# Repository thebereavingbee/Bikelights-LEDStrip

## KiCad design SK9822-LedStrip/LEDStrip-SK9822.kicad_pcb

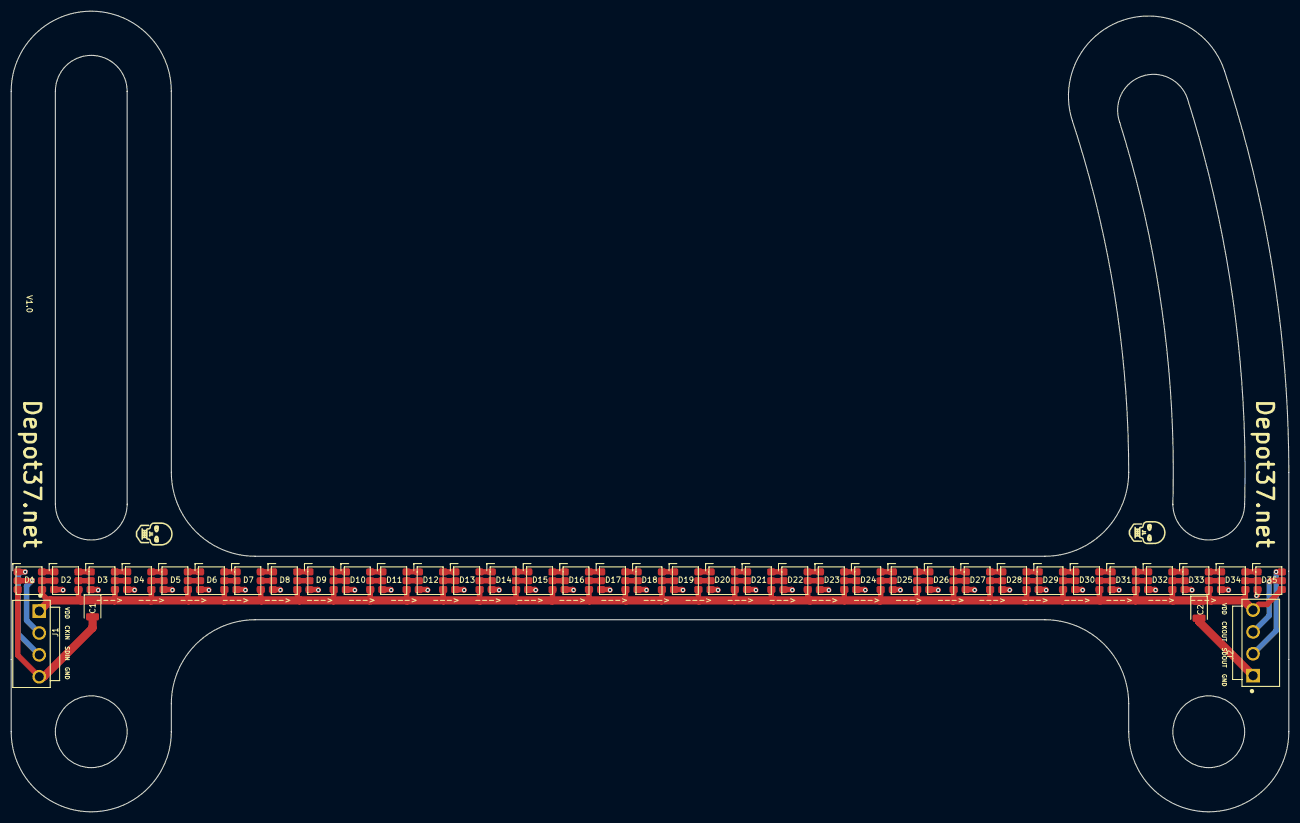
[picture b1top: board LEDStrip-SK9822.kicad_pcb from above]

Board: 2 copper layers, 231.4 x 145.0 mm, 39 parts (0 on the bottom side), 74 nets.

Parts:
C1, C2: 100uF; CP_EIA-3528-15_AVX-H
D1, D2, D3, D4, D5, D6, D7, D8, D9, D10, D11, D12, D13, D14, D15, D16, D17, D18, D19, D20, D21, D22, D23, D24, D25, D26, D27, D28, D29, D30, D31, D32, D33, D34, D35: SK9822
J1, J2: TE_1-1123723-4

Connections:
/CKIN: D1.2, J1.2
/CKOUT: D35.5, J2.3
/GND: C1.2, C2.2, D1.3, D2.3, D3.3, D4.3, D5.3, D6.3, D7.3, D8.3, D9.3, D10.3, D11.3, D12.3, D13.3, D14.3, D15.3, D16.3, D17.3, D18.3, D19.3, D20.3, D21.3, D22.3, D23.3, D24.3, D25.3, D26.3, D27.3, D28.3, D29.3, D30.3, D31.3, D32.3, D33.3, D34.3, D35.3, J1.4, J2.1
/SDIN: D1.1, J1.3
/SDOUT: D35.6, J2.2
/VDD: C1.1, C2.1, D1.4, D2.4, D3.4, D4.4, D5.4, D6.4, D7.4, D8.4, D9.4, D10.4, D11.4, D12.4, D13.4, D14.4, D15.4, D16.4, D17.4, D18.4, D19.4, D20.4, D21.4, D22.4, D23.4, D24.4, D25.4, D26.4, D27.4, D28.4, D29.4, D30.4, D31.4, D32.4, D33.4, D34.4, D35.4, J1.1, J2.4
unnamed: D1.5, D2.2
unnamed: D1.6, D2.1
unnamed: D2.5, D3.2
unnamed: D2.6, D3.1
unnamed: D3.5, D4.2
unnamed: D3.6, D4.1
unnamed: D4.5, D5.2
unnamed: D4.6, D5.1
unnamed: D5.5, D6.2
unnamed: D5.6, D6.1
unnamed: D6.5, D7.2
unnamed: D6.6, D7.1
unnamed: D7.5, D8.2
unnamed: D7.6, D8.1
unnamed: D8.5, D9.2
unnamed: D8.6, D9.1
unnamed: D9.6, D10.1
unnamed: D9.5, D10.2
unnamed: D10.5, D11.2
unnamed: D10.6, D11.1
unnamed: D11.5, D12.2
unnamed: D11.6, D12.1
unnamed: D12.5, D13.2
unnamed: D12.6, D13.1
unnamed: D13.5, D14.2
unnamed: D13.6, D14.1
unnamed: D14.5, D15.2
unnamed: D14.6, D15.1
unnamed: D15.5, D16.2
unnamed: D15.6, D16.1
unnamed: D16.5, D17.2
unnamed: D16.6, D17.1
unnamed: D17.5, D18.2
unnamed: D17.6, D18.1
unnamed: D18.5, D19.2
unnamed: D18.6, D19.1
unnamed: D19.5, D20.2
unnamed: D19.6, D20.1
unnamed: D20.5, D21.2
unnamed: D20.6, D21.1
unnamed: D21.5, D22.2
unnamed: D21.6, D22.1
unnamed: D22.5, D23.2
unnamed: D22.6, D23.1
unnamed: D23.5, D24.2
unnamed: D23.6, D24.1
unnamed: D24.5, D25.2
unnamed: D24.6, D25.1
unnamed: D25.5, D26.2
unnamed: D25.6, D26.1
unnamed: D26.5, D27.2
unnamed: D26.6, D27.1
unnamed: D27.5, D28.2
unnamed: D27.6, D28.1
unnamed: D28.5, D29.2
unnamed: D28.6, D29.1
unnamed: D29.5, D30.2
unnamed: D29.6, D30.1
unnamed: D30.5, D31.2
unnamed: D30.6, D31.1
unnamed: D31.5, D32.2
unnamed: D31.6, D32.1
unnamed: D32.5, D33.2
unnamed: D32.6, D33.1
unnamed: D33.5, D34.2
unnamed: D33.6, D34.1
unnamed: D34.5, D35.2
unnamed: D34.6, D35.1

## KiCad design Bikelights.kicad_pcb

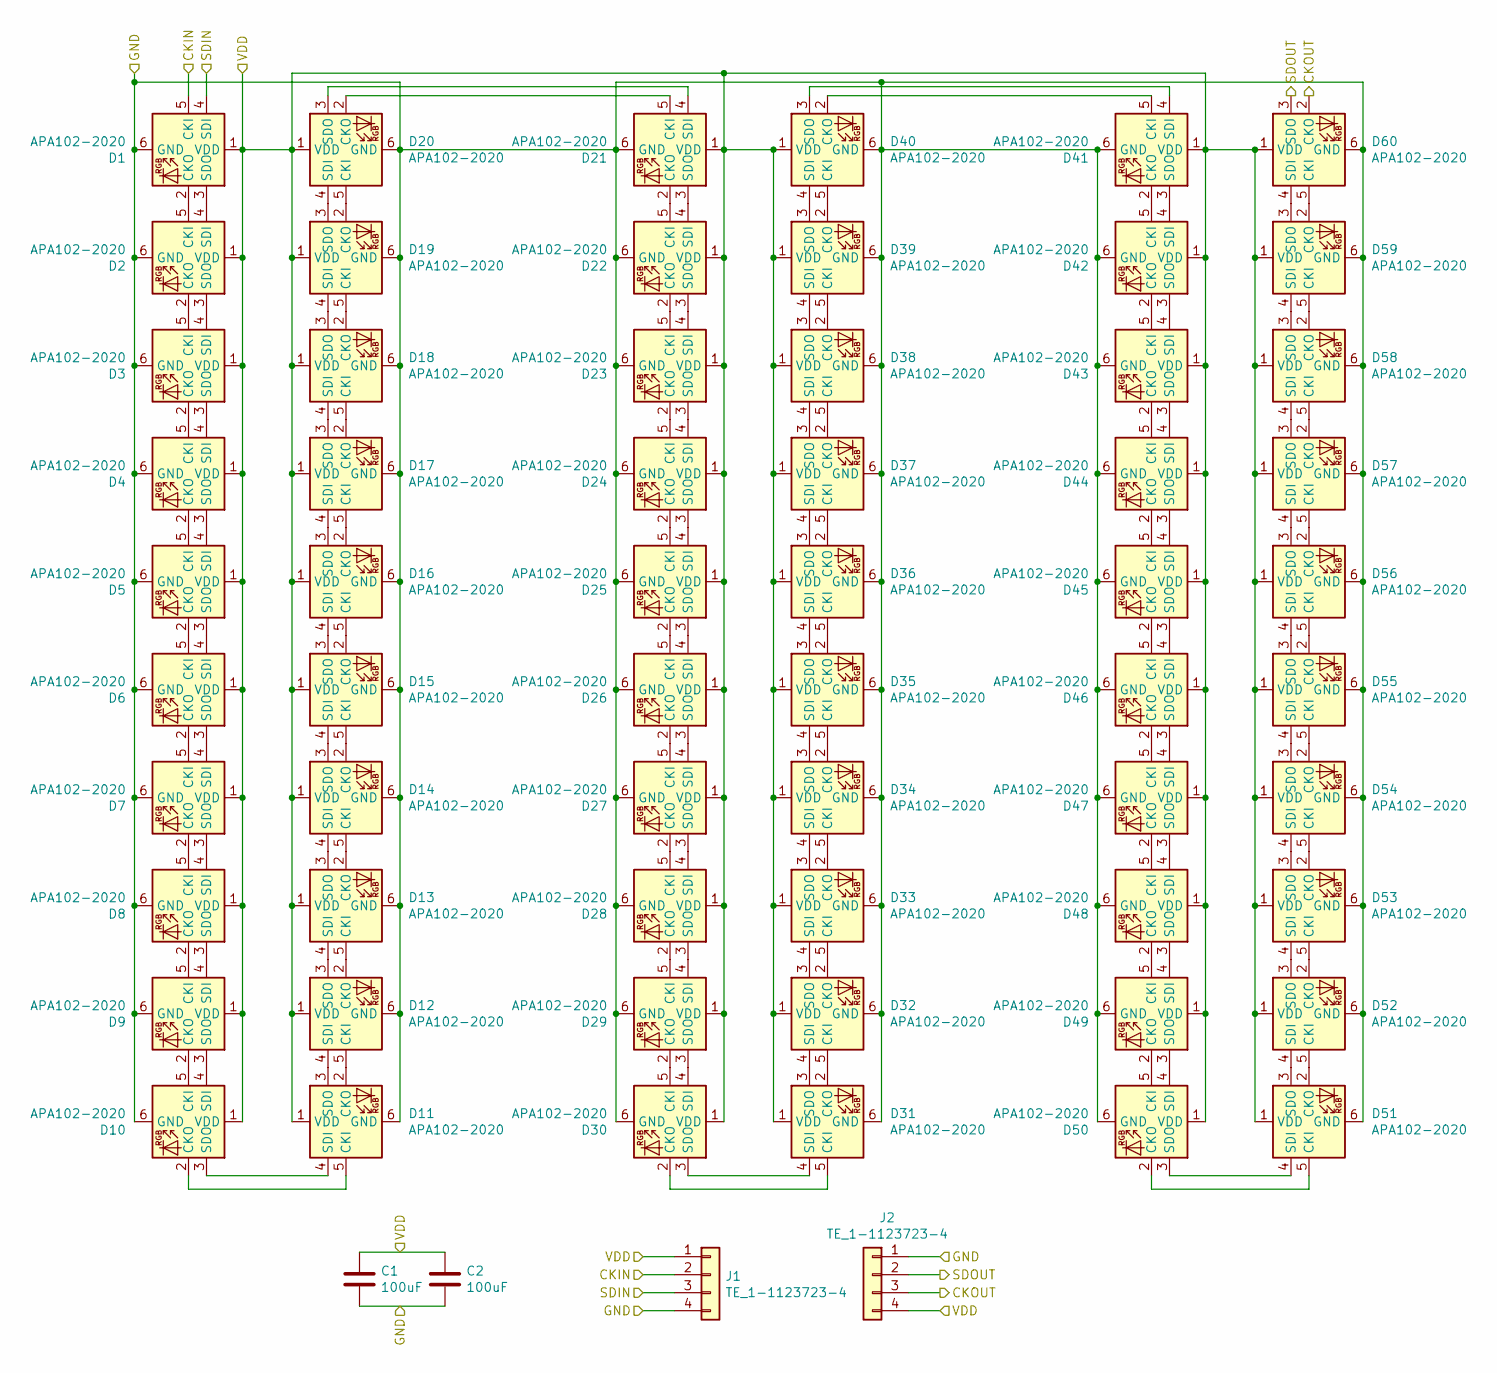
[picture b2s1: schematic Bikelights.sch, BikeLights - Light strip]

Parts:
C1, C2: 100uF; CP_EIA-3528-15_AVX-H
D1, D2, D3, D4, D5, D6, D7, D8, D9, D10, D11, D12, D13, D14, D15, D16, D17, D18, D19, D20, D21, D22, D23, D24, D25, D26, D27, D28, D29, D30, D31, D32, D33, D34, D35, D36, D37, D38, D39, D40, D41, D42, D43, D44, D45, D46, D47, D48, D49, D50, D51, D52, D53, D54, D55, D56, D57, D58, D59, D60: APA102-2020; LED-APA102-2020
J1, J2: TE_1-1123723-4

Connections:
/CKIN: D1.5 (CKI), J1.2
/CKOUT: D60.2 (CKO), J2.3
/GND: C1.2, C2.2, D1.6 (GND), D2.6 (GND), D3.6 (GND), D4.6 (GND), D5.6 (GND), D6.6 (GND), D7.6 (GND), D8.6 (GND), D9.6 (GND), D10.6 (GND), D11.6 (GND), D12.6 (GND), D13.6 (GND), D14.6 (GND), D15.6 (GND), D16.6 (GND), D17.6 (GND), D18.6 (GND), D19.6 (GND), D20.6 (GND), D21.6 (GND), D22.6 (GND), D23.6 (GND), D24.6 (GND), D25.6 (GND), D26.6 (GND), D27.6 (GND), D28.6 (GND), D29.6 (GND), D30.6 (GND), D31.6 (GND), D32.6 (GND), D33.6 (GND), D34.6 (GND), D35.6 (GND), D36.6 (GND), D37.6 (GND), D38.6 (GND), D39.6 (GND), D40.6 (GND), D41.6 (GND), D42.6 (GND), D43.6 (GND), D44.6 (GND), D45.6 (GND), D46.6 (GND), D47.6 (GND), D48.6 (GND), D49.6 (GND), D50.6 (GND), D51.6 (GND), D52.6 (GND), D53.6 (GND), D54.6 (GND), D55.6 (GND), D56.6 (GND), D57.6 (GND), D58.6 (GND), D59.6 (GND), D60.6 (GND), J1.4, J2.1
/SDIN: D1.4 (SDI), J1.3
/SDOUT: D60.3 (SDO), J2.2
/VDD: C1.1, C2.1, D1.1 (VDD), D2.1 (VDD), D3.1 (VDD), D4.1 (VDD), D5.1 (VDD), D6.1 (VDD), D7.1 (VDD), D8.1 (VDD), D9.1 (VDD), D10.1 (VDD), D11.1 (VDD), D12.1 (VDD), D13.1 (VDD), D14.1 (VDD), D15.1 (VDD), D16.1 (VDD), D17.1 (VDD), D18.1 (VDD), D19.1 (VDD), D20.1 (VDD), D21.1 (VDD), D22.1 (VDD), D23.1 (VDD), D24.1 (VDD), D25.1 (VDD), D26.1 (VDD), D27.1 (VDD), D28.1 (VDD), D29.1 (VDD), D30.1 (VDD), D31.1 (VDD), D32.1 (VDD), D33.1 (VDD), D34.1 (VDD), D35.1 (VDD), D36.1 (VDD), D37.1 (VDD), D38.1 (VDD), D39.1 (VDD), D40.1 (VDD), D41.1 (VDD), D42.1 (VDD), D43.1 (VDD), D44.1 (VDD), D45.1 (VDD), D46.1 (VDD), D47.1 (VDD), D48.1 (VDD), D49.1 (VDD), D50.1 (VDD), D51.1 (VDD), D52.1 (VDD), D53.1 (VDD), D54.1 (VDD), D55.1 (VDD), D56.1 (VDD), D57.1 (VDD), D58.1 (VDD), D59.1 (VDD), D60.1 (VDD), J1.1, J2.4
unnamed: D1.2 (CKO), D2.5 (CKI)
unnamed: D1.3 (SDO), D2.4 (SDI)
unnamed: D2.2 (CKO), D3.5 (CKI)
unnamed: D2.3 (SDO), D3.4 (SDI)
unnamed: D3.2 (CKO), D4.5 (CKI)
unnamed: D3.3 (SDO), D4.4 (SDI)
unnamed: D4.2 (CKO), D5.5 (CKI)
unnamed: D4.3 (SDO), D5.4 (SDI)
unnamed: D5.2 (CKO), D6.5 (CKI)
unnamed: D5.3 (SDO), D6.4 (SDI)
unnamed: D6.2 (CKO), D7.5 (CKI)
unnamed: D6.3 (SDO), D7.4 (SDI)
unnamed: D7.2 (CKO), D8.5 (CKI)
unnamed: D7.3 (SDO), D8.4 (SDI)
unnamed: D8.2 (CKO), D9.5 (CKI)
unnamed: D8.3 (SDO), D9.4 (SDI)
unnamed: D10.2 (CKO), D11.5 (CKI)
unnamed: D10.3 (SDO), D11.4 (SDI)
unnamed: D9.3 (SDO), D10.4 (SDI)
unnamed: D9.2 (CKO), D10.5 (CKI)
unnamed: D11.2 (CKO), D12.5 (CKI)
unnamed: D11.3 (SDO), D12.4 (SDI)
unnamed: D12.2 (CKO), D13.5 (CKI)
unnamed: D12.3 (SDO), D13.4 (SDI)
unnamed: D13.2 (CKO), D14.5 (CKI)
unnamed: D13.3 (SDO), D14.4 (SDI)
unnamed: D14.2 (CKO), D15.5 (CKI)
unnamed: D14.3 (SDO), D15.4 (SDI)
unnamed: D15.2 (CKO), D16.5 (CKI)
unnamed: D15.3 (SDO), D16.4 (SDI)
unnamed: D16.2 (CKO), D17.5 (CKI)
unnamed: D16.3 (SDO), D17.4 (SDI)
unnamed: D17.2 (CKO), D18.5 (CKI)
unnamed: D17.3 (SDO), D18.4 (SDI)
unnamed: D18.2 (CKO), D19.5 (CKI)
unnamed: D18.3 (SDO), D19.4 (SDI)
unnamed: D19.2 (CKO), D20.5 (CKI)
unnamed: D19.3 (SDO), D20.4 (SDI)
unnamed: D20.2 (CKO), D21.5 (CKI)
unnamed: D20.3 (SDO), D21.4 (SDI)
unnamed: D21.2 (CKO), D22.5 (CKI)
unnamed: D21.3 (SDO), D22.4 (SDI)
unnamed: D22.2 (CKO), D23.5 (CKI)
unnamed: D22.3 (SDO), D23.4 (SDI)
unnamed: D23.2 (CKO), D24.5 (CKI)
unnamed: D23.3 (SDO), D24.4 (SDI)
unnamed: D24.2 (CKO), D25.5 (CKI)
unnamed: D24.3 (SDO), D25.4 (SDI)
unnamed: D25.2 (CKO), D26.5 (CKI)
unnamed: D25.3 (SDO), D26.4 (SDI)
unnamed: D26.2 (CKO), D27.5 (CKI)
unnamed: D26.3 (SDO), D27.4 (SDI)
unnamed: D27.2 (CKO), D28.5 (CKI)
unnamed: D27.3 (SDO), D28.4 (SDI)
unnamed: D28.2 (CKO), D29.5 (CKI)
unnamed: D28.3 (SDO), D29.4 (SDI)
unnamed: D29.2 (CKO), D30.5 (CKI)
unnamed: D29.3 (SDO), D30.4 (SDI)
unnamed: D30.2 (CKO), D31.5 (CKI)
unnamed: D30.3 (SDO), D31.4 (SDI)
unnamed: D31.2 (CKO), D32.5 (CKI)
unnamed: D31.3 (SDO), D32.4 (SDI)
unnamed: D32.2 (CKO), D33.5 (CKI)
unnamed: D32.3 (SDO), D33.4 (SDI)
unnamed: D33.2 (CKO), D34.5 (CKI)
unnamed: D33.3 (SDO), D34.4 (SDI)
unnamed: D34.2 (CKO), D35.5 (CKI)
unnamed: D34.3 (SDO), D35.4 (SDI)
unnamed: D35.2 (CKO), D36.5 (CKI)
unnamed: D35.3 (SDO), D36.4 (SDI)
unnamed: D36.2 (CKO), D37.5 (CKI)
unnamed: D36.3 (SDO), D37.4 (SDI)
unnamed: D37.2 (CKO), D38.5 (CKI)
unnamed: D37.3 (SDO), D38.4 (SDI)
unnamed: D38.2 (CKO), D39.5 (CKI)
unnamed: D38.3 (SDO), D39.4 (SDI)
unnamed: D39.2 (CKO), D40.5 (CKI)
unnamed: D39.3 (SDO), D40.4 (SDI)
unnamed: D40.2 (CKO), D41.5 (CKI)
unnamed: D40.3 (SDO), D41.4 (SDI)
unnamed: D41.2 (CKO), D42.5 (CKI)
unnamed: D41.3 (SDO), D42.4 (SDI)
unnamed: D42.2 (CKO), D43.5 (CKI)
unnamed: D42.3 (SDO), D43.4 (SDI)
unnamed: D43.2 (CKO), D44.5 (CKI)
unnamed: D43.3 (SDO), D44.4 (SDI)
unnamed: D44.2 (CKO), D45.5 (CKI)
unnamed: D44.3 (SDO), D45.4 (SDI)
unnamed: D45.2 (CKO), D46.5 (CKI)
unnamed: D45.3 (SDO), D46.4 (SDI)
unnamed: D46.2 (CKO), D47.5 (CKI)
unnamed: D46.3 (SDO), D47.4 (SDI)
unnamed: D47.2 (CKO), D48.5 (CKI)
unnamed: D47.3 (SDO), D48.4 (SDI)
unnamed: D48.2 (CKO), D49.5 (CKI)
unnamed: D48.3 (SDO), D49.4 (SDI)
unnamed: D49.2 (CKO), D50.5 (CKI)
unnamed: D49.3 (SDO), D50.4 (SDI)
unnamed: D50.2 (CKO), D51.5 (CKI)
unnamed: D50.3 (SDO), D51.4 (SDI)
unnamed: D51.2 (CKO), D52.5 (CKI)
unnamed: D51.3 (SDO), D52.4 (SDI)
unnamed: D52.2 (CKO), D53.5 (CKI)
unnamed: D52.3 (SDO), D53.4 (SDI)
unnamed: D53.2 (CKO), D54.5 (CKI)
unnamed: D53.3 (SDO), D54.4 (SDI)
unnamed: D54.2 (CKO), D55.5 (CKI)
unnamed: D54.3 (SDO), D55.4 (SDI)
unnamed: D55.2 (CKO), D56.5 (CKI)
unnamed: D55.3 (SDO), D56.4 (SDI)
unnamed: D56.2 (CKO), D57.5 (CKI)
unnamed: D56.3 (SDO), D57.4 (SDI)
unnamed: D57.2 (CKO), D58.5 (CKI)
unnamed: D57.3 (SDO), D58.4 (SDI)
unnamed: D58.2 (CKO), D59.5 (CKI)
unnamed: D58.3 (SDO), D59.4 (SDI)
unnamed: D59.2 (CKO), D60.5 (CKI)
unnamed: D59.3 (SDO), D60.4 (SDI)

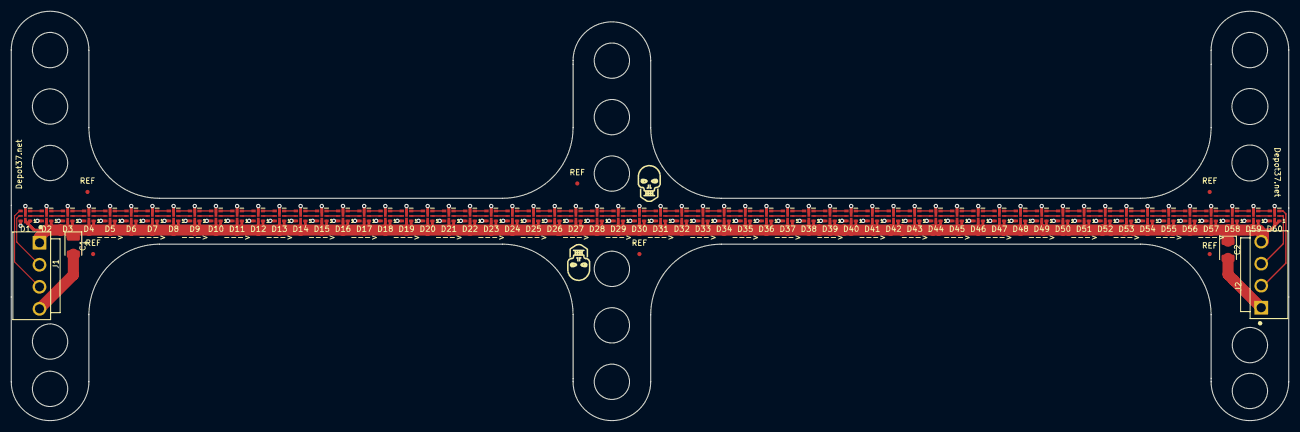
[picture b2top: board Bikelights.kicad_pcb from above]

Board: 2 copper layers, 229.9 x 73.7 mm, 70 parts (0 on the bottom side), 124 nets.

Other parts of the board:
REF: Fiducial_0.75mm_Mask1.5mm
REF#2, REF#3, REF#4, REF#5, REF#6: Fiducial_0.75mm_Mask1.5mm

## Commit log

2021-11-30 6 wing APA102-2020 9in design
2021-11-30 Organize different revisions
2021-11-30 Removed files in main directory
2021-11-30 Creating footprint for sk9822 and changing schematic to use sk9822
2021-11-30 Connecting pads on SK9822 and changing edge cut to better hold footprints
2021-11-30 Removing erronious files
2021-11-30 Adding Depot 37 logo and removing wings from the middle of sk9822 pcb
2021-11-30 Exporting PDF Sheet Nov-30-2021
2022-03-30 Prepared for mounting hardware
    This version has the straight mounting wings
2022-03-30 Curved Mounting Wing
2022-03-30 Save after exporting gbr
2022-06-14 Create new schematic for logic board
